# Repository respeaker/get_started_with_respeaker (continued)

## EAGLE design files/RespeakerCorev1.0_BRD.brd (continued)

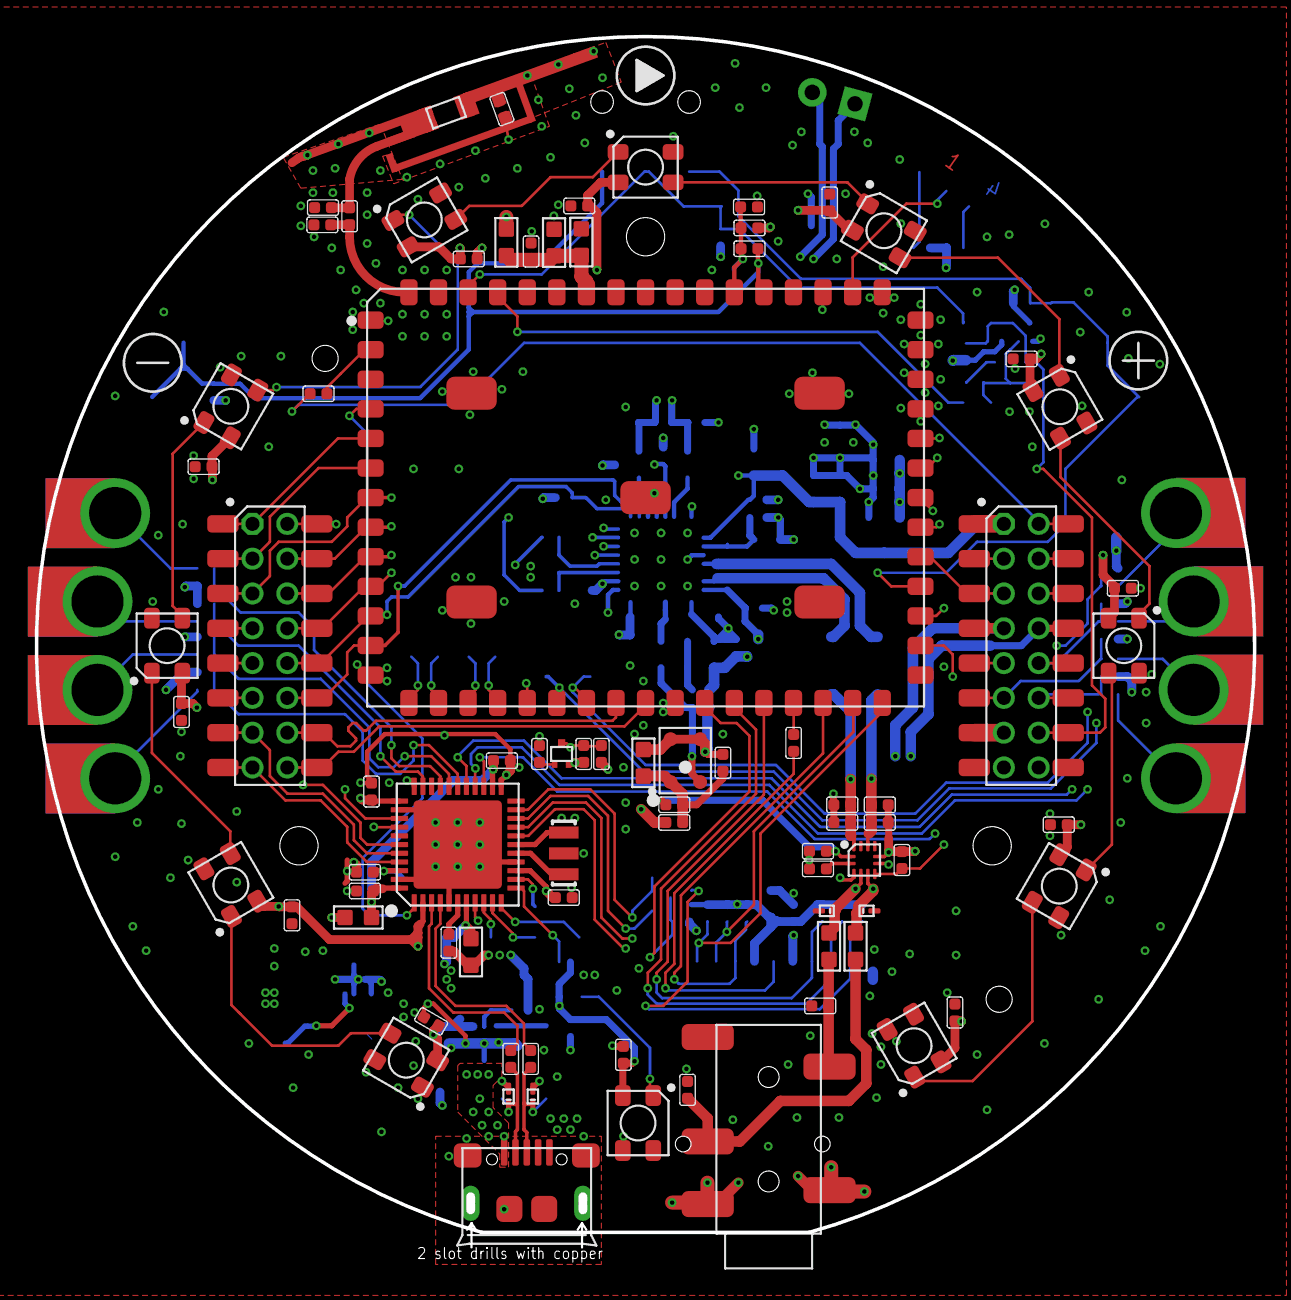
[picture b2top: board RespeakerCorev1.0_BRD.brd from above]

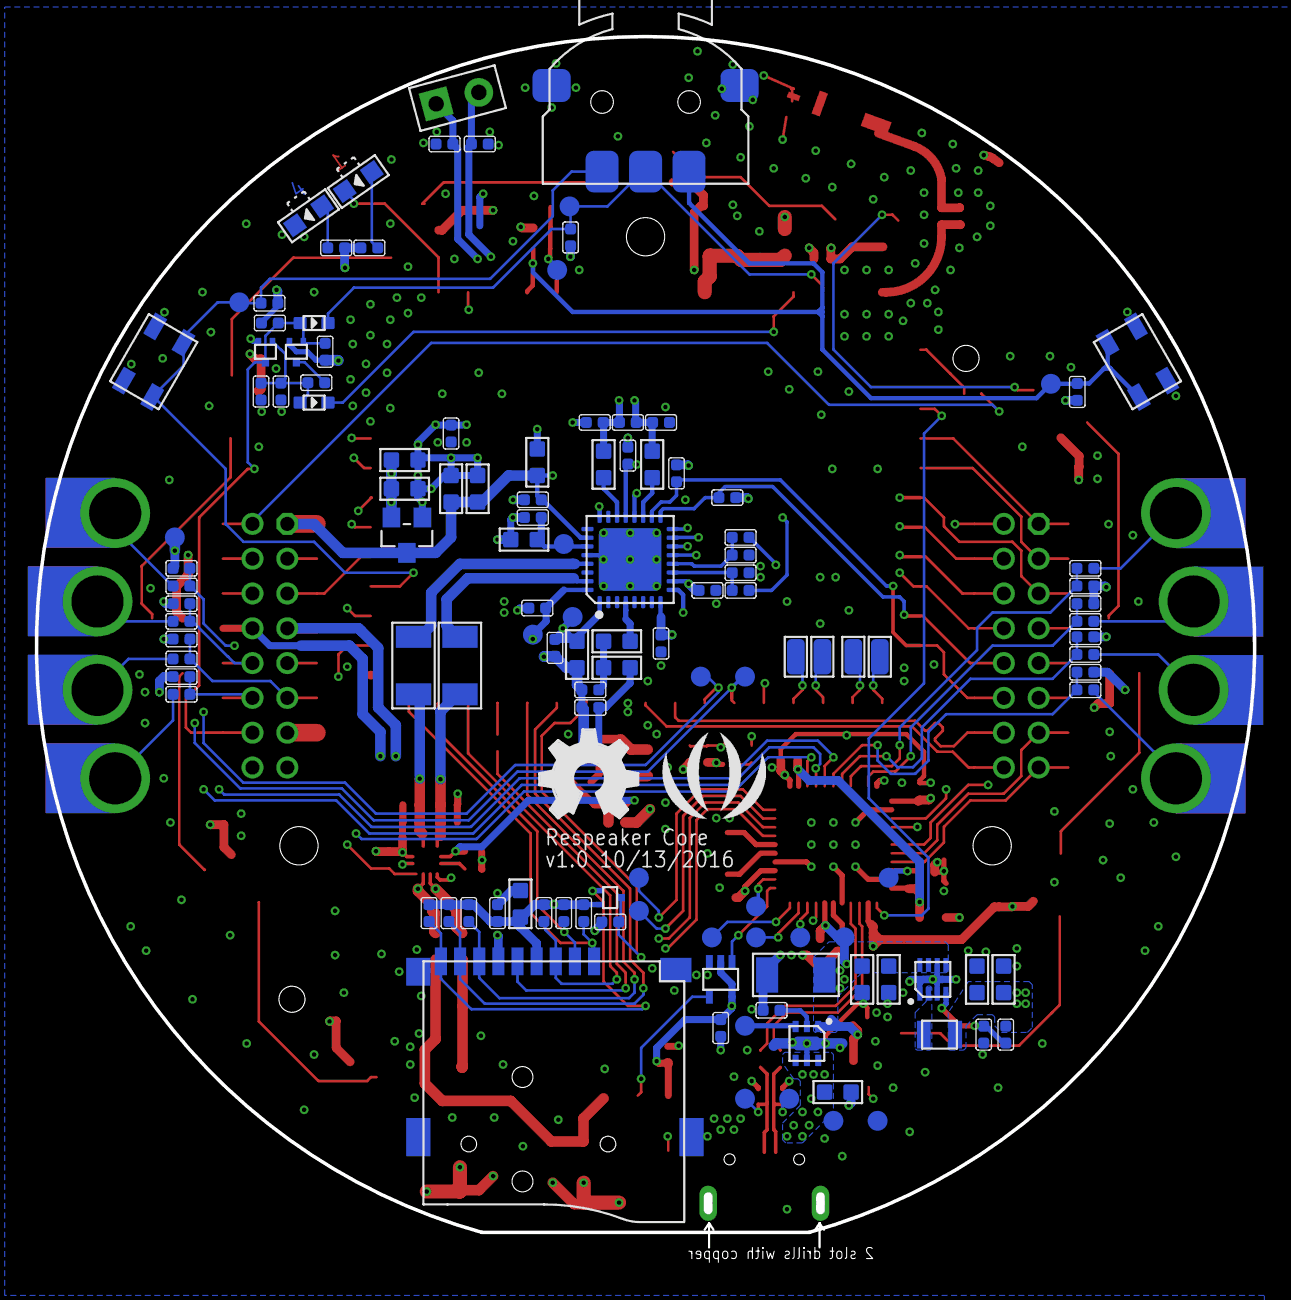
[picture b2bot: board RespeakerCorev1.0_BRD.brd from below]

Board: 4 copper layers, 70.0 x 69.6 mm, 220 parts (126 on the bottom side), 129 nets.

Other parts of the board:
U$75: OSHW_FILLX200_NOTEXT_TNAME
U$76: SEEED-SILK-TNAME-280*268MIL

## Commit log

2016-07-19 add usb serial driver for lpc11u35 on respeaker
2016-07-19 hardware files
2016-07-19 add components layout
2016-07-24 add tornado
2016-11-15 updated wiki
2016-11-17 updated programming guide
2016-11-20 update mopidy
2016-11-21 updated api introduction
2016-11-21 create respeaker core schematic
2016-11-21 create system-update
2016-11-22 update py api
2016-11-23 fix bug
2016-11-24 update introduction of software
2016-11-24 Syntax on and fix typo
2016-11-24 Syntax on
2016-11-24 replace wifi1 pic
2016-11-25 update exroot
2016-11-25 create airplay
2016-11-25 create dlna
2016-11-28 create pinout diagram
2016-11-28 updated pinout diagram
2016-11-29 updated pin map
2016-11-30 updated python libarary class microphone
2016-11-30 updated pin out introduction
2016-11-30 updated respeaker pro case 3d
2016-12-01 updated 'update for old version'
2016-12-02 created setup putty
2016-12-02 updated setup putty
2016-12-02 add mic array settings' protocol file
2016-12-07 create ReSpeaker_Pro_Case_Assembly_Instructions
2016-12-12 updated hardware information of mic array
2016-12-12 create respeaker mic array hid tool& driver
2016-12-16 add alexa ipk
2016-12-18 add micarray.png
2016-12-19 add try mycroft on respeaker
2016-12-19 updated 'Use SD Card to Extend Storage'
2016-12-20 fix respeakercorev1.0_schematic.pdf
2017-01-18 add alexa_2017-01-18_ramips_24kec.ipk
2017-01-23 fixed incorrect MP3 filename in the bing demo
2017-02-06 add link to respeaker mic array firmware and link to mic array sch&pcb
2017-02-21 add factoryreset & faq, edit First impression with voice interaction
2017-02-22 add usb storage connection picture
2017-03-02 add snapcast server and client ipk
2017-03-23 Fixed headers
    Added spaces after #'s to let headers render in GitHub.
2017-03-29 fix markdown bug
2017-04-05 fix format bug
2017-04-05 updated faq.md
2017-04-07 add facebook link
2017-04-07 fix link bug
2017-04-14 add schematic of respeaker grove extension board
2017-09-06 add ReSpeaker Core V2
2017-09-06 update respeaker v2
2017-09-06 update google drive
2017-09-07 update baiduyunpan
2017-09-19 Update getting_started.md
    few small verbiage changes, changed compress to unzip in mmc instructions section
2017-09-19 Update getting_started.md
    ifconfig is not on the Debian install (at least when flashing the image eMMC), instead of ifconfig, the command "ip address" can be used to get the ip address of the respeaker
2017-09-19 Update getting_started.md
    Added instructions on how to do the serial connection with an Arduino in the event the user does not have a USB to TTL cable
2017-09-20 Update getting_started.md
    English corrections and some additional verbiage to make the instructions more user friendly
2017-09-22 add image files for header pin
2017-09-22 resize the images
2017-09-25 add old_way_flash_emmc.md
2017-09-27 Update getting_started.md
    English corrections
2017-10-10 add onedrive
2017-10-11 add image files for the ReSpeaker Drive Unit
2017-10-12 ReSpeaker Drive Unit
2017-10-12 fix text indent
2017-10-12 update ReSpeaker Drive Unit's image share url
2017-10-12 update music stream
2017-10-12 fix typo of streaming music
2017-10-12 fix typo again
2017-10-23 Updated ReSpeaker Drive Unit section
    to make the missing packages (and get them back again) crystal clear
2017-11-17 update firmware url
2017-11-21 add mraa and upm wiki
2017-11-21 update getting started for respeaker core v2 on serial console
2017-11-21 update getting started for respeaker core v2 on serial console [2]
2017-11-23 add hdmi , gpu ,vpu index
2017-11-23 add hdmi,gpu,vpu page
2017-11-27 add chinese respeaker v2 get started
2017-11-27 add chinese doc link
2017-11-28 fix anchor link
2017-11-28 add bluetooth_audio docments
2017-11-28 fix path 404 error
2017-11-28 fix link error
2017-11-29 add respeaker v2 Gadget CDC driver
2017-11-29 fix path
2017-11-29 update links for the libraries
2017-11-29 fix missing packages for avs
2017-11-29 add offline version of google assistant
2017-11-29 apt-get -> apt, to make it concordant with former
2017-11-30 add kernel update steps
2017-11-30 add PIR sensor example
2017-11-30 add UPM example code for the TH02 temperature and humidity sensor
2017-11-30 fix unnecessary imports for the PIR sensor example
2017-12-01 fix image download link in Flash eMMC section
    drop the baidu and google drive links!
2017-12-11 update getting_started.md of ReSpeaker Core v2
    update the alsa and pulse setting
2018-01-03 update: docs/ReSpeaker_Core_V2/README.md, change the URL
2018-01-08 update respeaker v2 getting_started.md on the VNC usage
2018-01-08 update respeaker v2 getting_started.md, on vnc screenshot
2018-01-09 update respeaker v2 getting_started.md, finish TODOs.
2018-01-12 add docker_installation_guide.md, not activated at index yet, waiting the system image release
2018-01-12 update docker_installation_guide.md, fix typos
2018-02-08 Update graphics_and_display.md
    more clear description about the software, fix grammar
2018-02-10 Update getting_started.md
    update test procedure
2018-02-25 update docs/ReSpeaker_Core_V2/README.md
    add explanation about the difference between this wiki and the one in wiki.seeed.cc.
2018-02-25 update docs/ReSpeaker_Core_V2/getting_started.md
    add explanation about the difference between this wiki and the one in wiki.seeed.cc.
2018-02-25 update docs/ReSpeaker_Core_V2/README.md
    remove alsa and pulseaudio setting
2018-02-25 update wiki
2018-02-26 docs/ReSpeaker_Core_V2/README.md
    remove Voice Engine Settings, and move it into the AVS guide.
2018-02-26 update docs/ReSpeaker_Core_V2/README.md
    fix typo for AVS
2018-02-26 update docs/ReSpeaker_Core_V2/avs_guide.md and docs/ReSpeaker_Core_V2/getting_started.md delete unecessary paragraphs for old version system
2018-02-26 update docs/ReSpeaker_Core_V2/avs_guide.md, docs/ReSpeaker_Core_V2/getting_started.md, docs/ReSpeaker_Core_V2/README.md fix typos, fix formats, re-arrange TOC
2018-02-26 update docs/ReSpeaker_Core_V2/getting_started.md fix links and grammars
2018-02-26 update docs/ReSpeaker_Core_V2/avs_guide.md, docs/ReSpeaker_Core_V2/getting_started.md add "Connect Speaker or Headset", update "flash emmc"
2018-03-13 add out of box demo, add foretell of avs c++ sdk
2018-03-13 fix oob.md, clarify the system image version limitation
2018-03-20 update docs/ReSpeaker_Core_V2/avs_cpp_sdk.md, small fixes
2018-03-21 bluetooth_audio redirect to wiki
2018-03-21 add respeaker v2 case
2018-03-22 Update avs_cpp_sdk.md
    fix typo
2018-03-23 Update avs_cpp_sdk.md
    fix wrong commands
2018-03-30 update docs/ReSpeaker_Core_V2/README.md, add google assistant guide link
2018-06-06 use the new onedrive
2018-08-23 Update Introduction.md
    The old URL "https://github.com/respeaker/get_started_with_respeaker/blob/master/ReSpeakerArduinoLibrary.md#respeaker-arduino-library" is missing. I change URL to "https://github.com/respeaker/respea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
2021-01-28 Update getting_started.md
    Updating usb-tty for FreeBSD
